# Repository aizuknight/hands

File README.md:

# hands
**hands** is a keyboard which has 36 keys in total. I had been struggling with touch typing on QWERTY + row staggered keyboards. They are literally inefficient to type with, especially special keys like `ESC`, `Shift`, `Ctrl`, `Back Space`, `Enter/Return` and arrow keys. I had to forcely extend my fingers or move my hands. That's very annoying and tiring. **hands** solves this problem with split thumb keys and "Tap and Hold".

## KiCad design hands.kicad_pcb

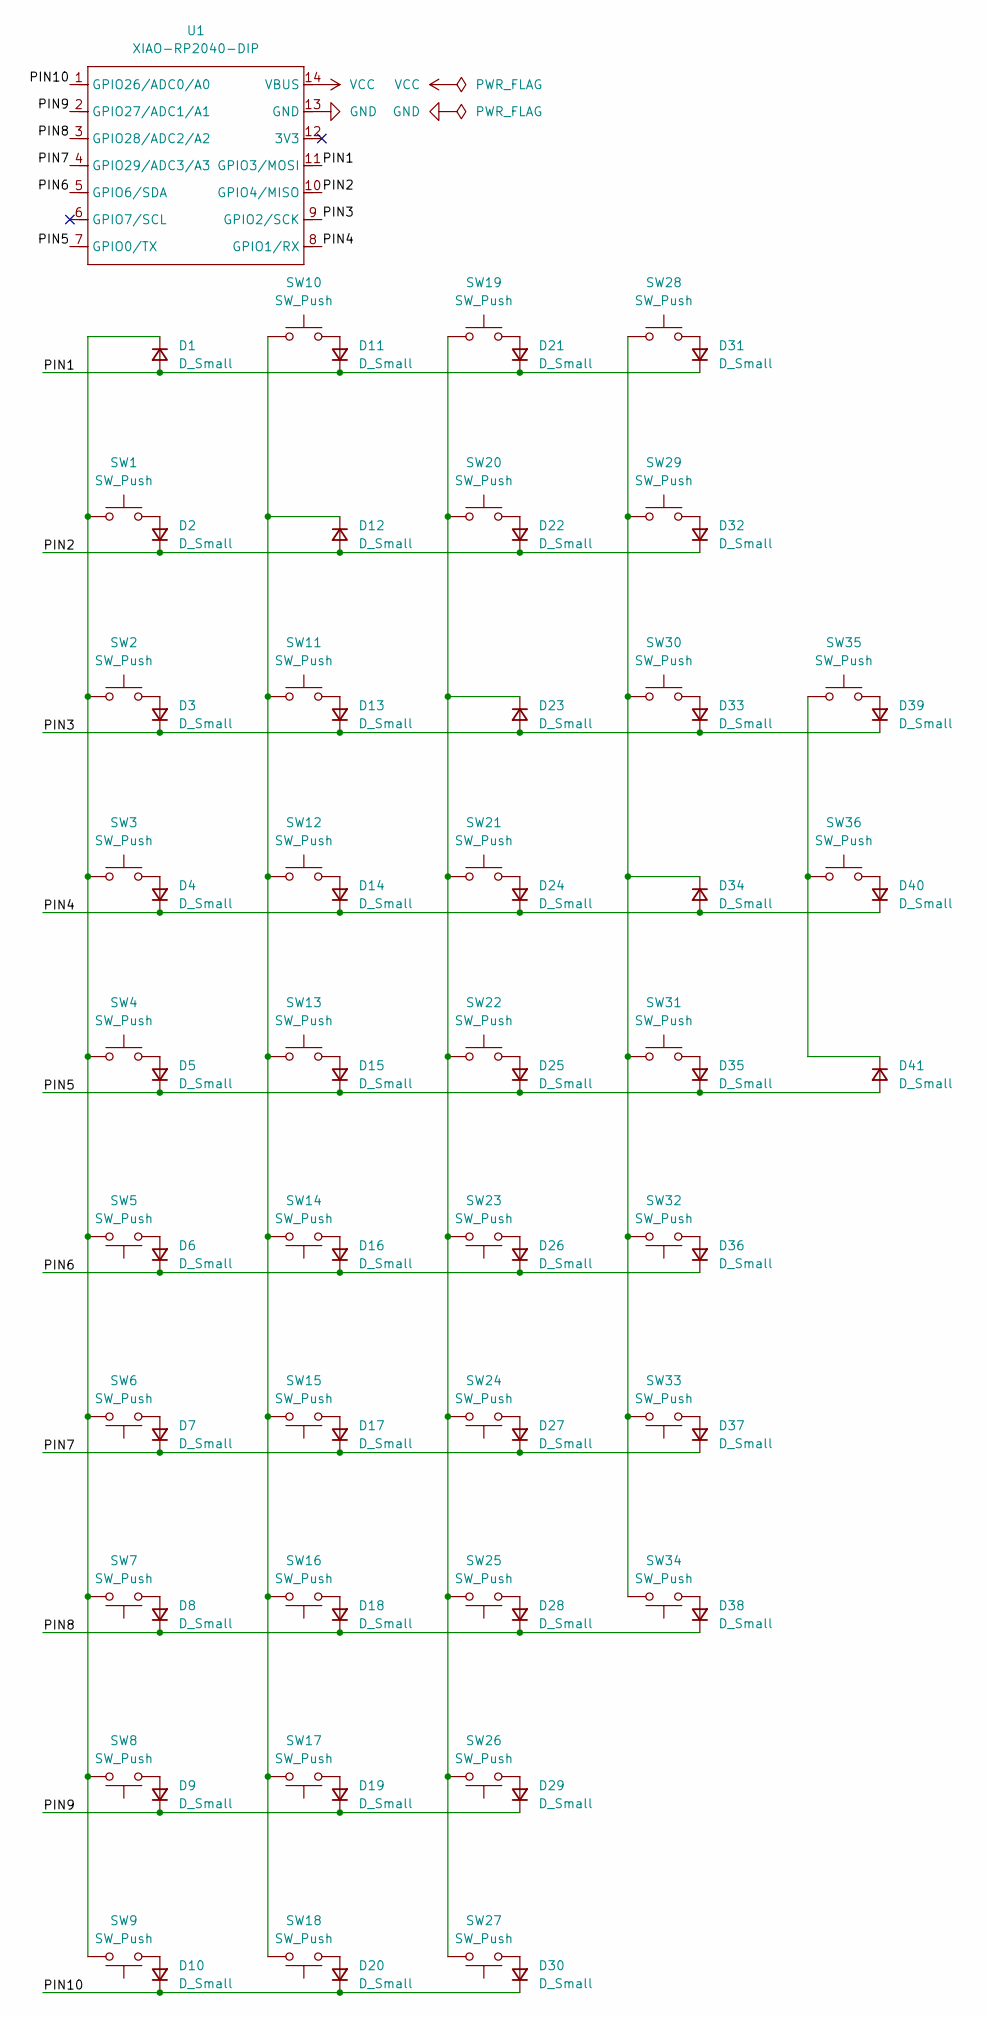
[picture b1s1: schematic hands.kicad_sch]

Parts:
D1, D2, D3, D4, D5, D6, D7, D8, D9, D10, D11, D12, D13, D14, D15, D16, D17, D18, D19, D20, D21, D22, D23, D24, D25, D26, D27, D28, D29, D30, D31, D32, D33, D34, D35, D36, D37, D38, D39, D40, D41: D_Small; D3_SMD_v2
SW1, SW2, SW3, SW4, SW5, SW6, SW7, SW8, SW9, SW10, SW11, SW12, SW13, SW14, SW15, SW16, SW17, SW18, SW19, SW20, SW21, SW22, SW23, SW24, SW25, SW26, SW27, SW28, SW29, SW30, SW31, SW32, SW34, SW35: SW_Push; CherryMX_Hotswap
SW33, SW36: SW_Push; CherryMX_Hotswap_1.5u
U1: XIAO-RP2040-DIP

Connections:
/PIN1: D1.2 (A), D11.1 (K), D21.1 (K), D31.1 (K), U1.11 (GPIO3/MOSI)
/PIN2: D2.1 (K), D12.2 (A), D22.1 (K), D32.1 (K), U1.10 (GPIO4/MISO)
/PIN3: D3.1 (K), D13.1 (K), D23.2 (A), D33.1 (K), D39.1 (K), U1.9 (GPIO2/SCK)
/PIN4: D4.1 (K), D14.1 (K), D24.1 (K), D34.2 (A), D40.1 (K), U1.8 (GPIO1/RX)
/PIN5: D5.1 (K), D15.1 (K), D25.1 (K), D35.1 (K), D41.2 (A), U1.7 (GPIO0/TX)
/PIN6: D6.1 (K), D16.1 (K), D26.1 (K), D36.1 (K), U1.5 (GPIO6/SDA)
/PIN7: D7.1 (K), D17.1 (K), D27.1 (K), D37.1 (K), U1.4 (GPIO29/ADC3/A3)
/PIN8: D8.1 (K), D18.1 (K), D28.1 (K), D38.1 (K), U1.3 (GPIO28/ADC2/A2)
/PIN9: D9.1 (K), D19.1 (K), D29.1 (K), U1.2 (GPIO27/ADC1/A1)
/PIN10: D10.1 (K), D20.1 (K), D30.1 (K), U1.1 (GPIO26/ADC0/A0)
GND: U1.13 (GND)
unnamed: D1.1 (K), SW1.1, SW2.1, SW3.1, SW4.1, SW5.2, SW6.2, SW7.2, SW8.2, SW9.2
unnamed: D2.2 (A), SW1.2
unnamed: D3.2 (A), SW2.2
unnamed: D4.2 (A), SW3.2
unnamed: D5.2 (A), SW4.2
unnamed: D6.2 (A), SW5.1
unnamed: D7.2 (A), SW6.1
unnamed: D8.2 (A), SW7.1
unnamed: D9.2 (A), SW8.1
unnamed: D10.2 (A), SW9.1
unnamed: D11.2 (A), SW10.2
unnamed: D12.1 (K), SW10.1, SW11.1, SW12.1, SW13.1, SW14.2, SW15.2, SW16.2, SW17.2, SW18.2
unnamed: D13.2 (A), SW11.2
unnamed: D14.2 (A), SW12.2
unnamed: D15.2 (A), SW13.2
unnamed: D16.2 (A), SW14.1
unnamed: D17.2 (A), SW15.1
unnamed: D18.2 (A), SW16.1
unnamed: D19.2 (A), SW17.1
unnamed: D20.2 (A), SW18.1
unnamed: D21.2 (A), SW19.2
unnamed: D22.2 (A), SW20.2
unnamed: D23.1 (K), SW19.1, SW20.1, SW21.1, SW22.1, SW23.2, SW24.2, SW25.2, SW26.2, SW27.2
unnamed: D24.2 (A), SW21.2
unnamed: D25.2 (A), SW22.2
unnamed: D26.2 (A), SW23.1
unnamed: D27.2 (A), SW24.1
unnamed: D28.2 (A), SW25.1
unnamed: D29.2 (A), SW26.1
unnamed: D30.2 (A), SW27.1
unnamed: D31.2 (A), SW28.2
unnamed: D32.2 (A), SW29.2
unnamed: D33.2 (A), SW30.2
unnamed: D34.1 (K), SW28.1, SW29.1, SW30.1, SW31.1, SW32.2, SW33.2, SW34.2
unnamed: D35.2 (A), SW31.2
unnamed: D36.2 (A), SW32.1
unnamed: D37.2 (A), SW33.1
unnamed: D38.2 (A), SW34.1
unnamed: D39.2 (A), SW35.2
unnamed: D40.2 (A), SW36.2
unnamed: D41.1 (K), SW35.1, SW36.1
VCC: U1.14 (VBUS)

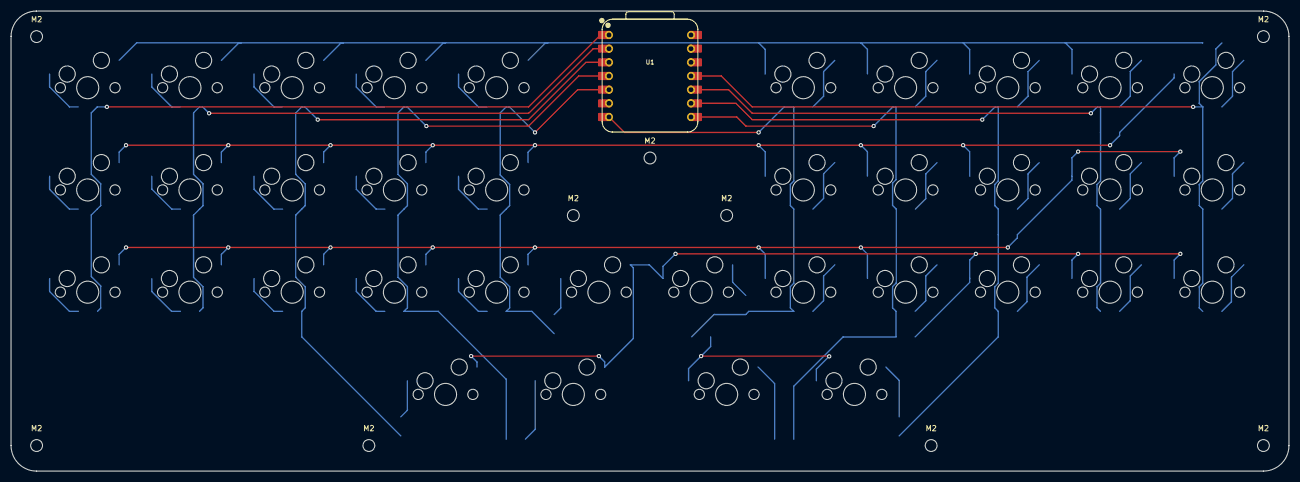
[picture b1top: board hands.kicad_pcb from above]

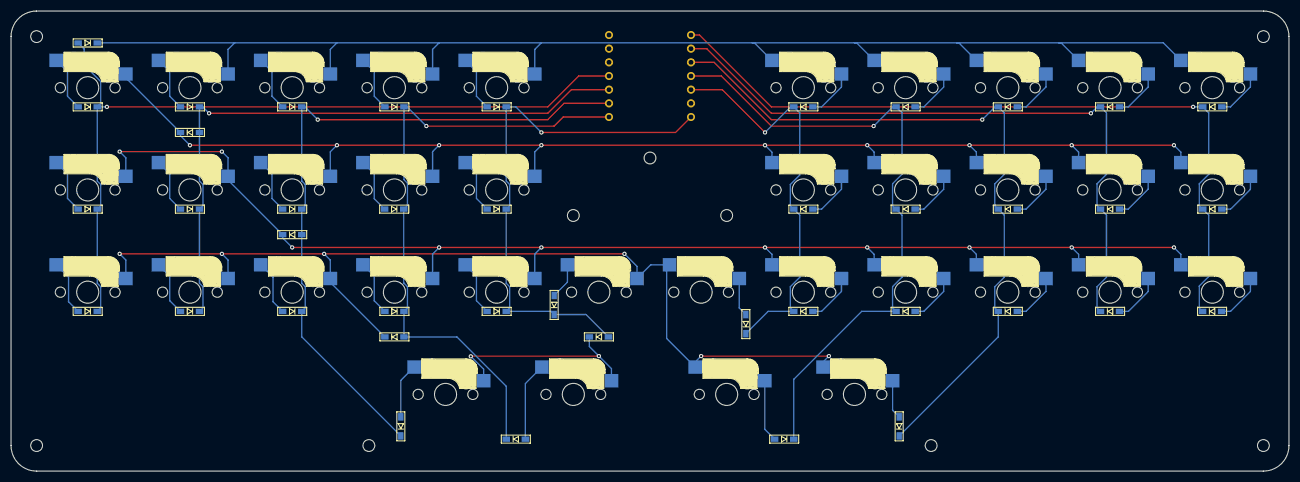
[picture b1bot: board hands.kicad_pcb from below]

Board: 2 copper layers, 237.5 x 85.5 mm, 87 parts (41 on the bottom side), 51 nets.

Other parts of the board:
M2, M2#2, M2#3, M2#4, M2#5, M2#6, M2#7, M2#8, M2#9: MountingHole_2.2mm_M2

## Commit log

2025-01-27 Fixed key pitch and added mounting hole
2026-04-20 Add description to README.md
2026-04-20 Move pcb design files to pcb directory
2026-06-03 Add firmware source code and build script
